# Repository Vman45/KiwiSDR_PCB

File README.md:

[updated 28 May 2018]

Click image for full size.

[© bluebison.net](http://bluebison.net)

KiwiSDR
=======

Software-defined Radio (SDR) and GPS for the BeagleBone Black
----------------------------------------------------------------------

An add-on board ("cape") that turns your Beagle into a web-accessible shortwave receiver.

This repository contains the KiCAD files (schematics, board layout), Gerbers, BOM and other files used to produce the KiwiSDR PCB.
Also included here is the design for an active antenna and bias tee.

**Note: the active antenna and bias tee schematics and PCBs here are still undergoing development and do not work properly. Do not fabricate the PCBs and expect them to work.**

The KiwiSDR software is located in the repository [Beagle_SDR_GPS](https://github.com/jks-prv/Beagle_SDR_GPS/).

### Kickstarter
KiwiSDR had a successful [Kickstarter](https://www.kickstarter.com/projects/1575992013/kiwisdr-beaglebone-software-defined-radio-sdr-with/).

### Details

* Listen live: [SDR.hu](https://sdr.hu/?top=kiwi), [kiwisdr.com](http://kiwisdr.com/public), [rx.linkfanel.net](http://rx.linkfanel.net)
* [Project webpage](http://www.kiwisdr.com/)
* [Operating information: installation, operation, FAQ](http://www.kiwisdr.com/quickstart/)
* Latest [source code commits](https://github.com/jks-prv/Beagle_SDR_GPS/commits/master)
* [Design review document](https://www.dropbox.com/s/i1bjyp1acghnc16/KiwiSDR.design.review.pdf?dl=1)
* [Schematic](http://www.kiwisdr.com/docs/KiwiSDR/kiwi.schematic.pdf), [Gerbers](http://www.kiwisdr.com/docs/KiwiSDR/kiwi.gerbers.tar), [Active antenna](http://www.kiwisdr.com/docs/KiwiSDR/ant.pdf), [BOM ODS](http://www.kiwisdr.com/docs/KiwiSDR/kiwi.bom.ods), [BOM XLS](http://www.kiwisdr.com/docs/KiwiSDR/kiwi.bom.xls)

### Description
This SDR is a bit different. It has a web interface that can be used by up to four separate listeners. Each one listening and tuning an independent frequency simultaneously. See the screenshots below.

### Components
* SDR covering the 10 kHz to 30 MHz (VLF-HF) spectrum.
* Web interface based on [OpenWebRX](http://openwebrx.org/) from András Retzler, HA7ILM.
* Integrated software-defined GPS receiver from Andrew Holme's [Homemade GPS Receiver](http://www.aholme.co.uk/GPS/Main.htm).
* LTC 14-bit 65 MHz ADC.
* Xilinx Artix-7 A35 FPGA.
* Skyworks SE4150L GPS front-end.

### Features
* 100% Open Source / Open Hardware.
* Browser-based interface allowing multiple simultaneous user web connections (currently 4).
* Each connection tunes an independent receiver channel over the entire spectrum.
* Waterfall tunes independently of audio and includes zooming and panning.
* Multi-channel, parallel DDC design using bit-width optimized CIC filters.
* Good performance at VLF/LF since we personally spend time monitoring those frequencies.
* Automatic frequency calibration via received GPS timing.
* Easy hardware and software setup. Browser-based configuration interface.

### Status

Give the live receivers a try at the links above. You'll need a recent version of a modern web browser that supports HTML5. The web interface works, with some problems, on mobile devices. But there is no mobile version of the interface yet.

The files of a KiCAD PCB layout of the cape are available. This PCB has been fabricated in production quantities
and shipped to thousands of customers worldwide.
Please email us any comments you have after reviewing the design document above. The active antenna and injector PCBs have been fabricated and are undergoing development.

### Objectives

We wanted to design an SDR that provides certain features, at a low price point, that we felt weren't covered by current devices. The SDR must be web-accessible and simple to setup and use.
We also wanted to provide a self-contained platform for experimentation with SDR and GPS techniques. 

Most importantly, We'd really like to see a significant number of web-enabled, wide-band SDRs deployed in diverse locations world-wide because that makes possible some really interesting applications and experiments.

### Operation

Users can purchase just the KiwiSDR board or a complete "kit" consisting of the board, BeagleBone Green (software pre-installed), enclosure (assembly required), and GPS antenna (see [here](http://www.kiwisdr.com/)).
The software will try to automatically open up an incoming port through whatever Internet firewall/router may exist on the local network, but the user may have to perform this step manually. An antenna solution must be provided. An adequate power supply to the Beagle (e.g. 5V @ 2A) will also be required.

Four channels of audio and waterfall streamed over the Internet 24/7 requires about 30 GB per month. This is a common cap for many residential broadband plans. An automatic dynamic-DNS system is already part of the software so a web link to the SDR is immediately available with no configuration. Of course the system can be configured to only allow connections from the local network and ignore Internet connection requests.

### Web interface screenshots

Click images for full size.

View of entire 0-30 MHz range:

Moderate zoom of medium-wave broadcast band with spectrum display on top enabled:

Over-the-horizon-radar (OTHR) from Cyprus showing short-term ionospheric fluctuations:

VLF/LF reception in New Zealand

| kHz | Station | Location | Signal |
| :-- | :------ | :------- | :----- |
| 12.88 | Alpha | Khabarovsk & Novosibirsk Russia | Navigation system |
| 17.0 | VTX2 | India | MSK comms |
| 19.8 | NWC | Australia | MSK comms |
| 21.4 | NPM | Hawaii | MSK comms |
| 22.2 | NDT/JJI | Japan | MSK comms |
| 24.1 | (UNID) | Korea, per David L Wilson | FSK comms |
| 40.0 | JJY | Japan | Time signal |
| 45.9 | NSY | Italy | MSK comms |
| 54.0 | NDI | Japan | MSK comms |
| 60.0 | JJY/WWVB | Japan, USA | Time signals |
| 68.5 | BPC | China | Time signal |

Many others heard during different times and conditions.

[end-of-document]

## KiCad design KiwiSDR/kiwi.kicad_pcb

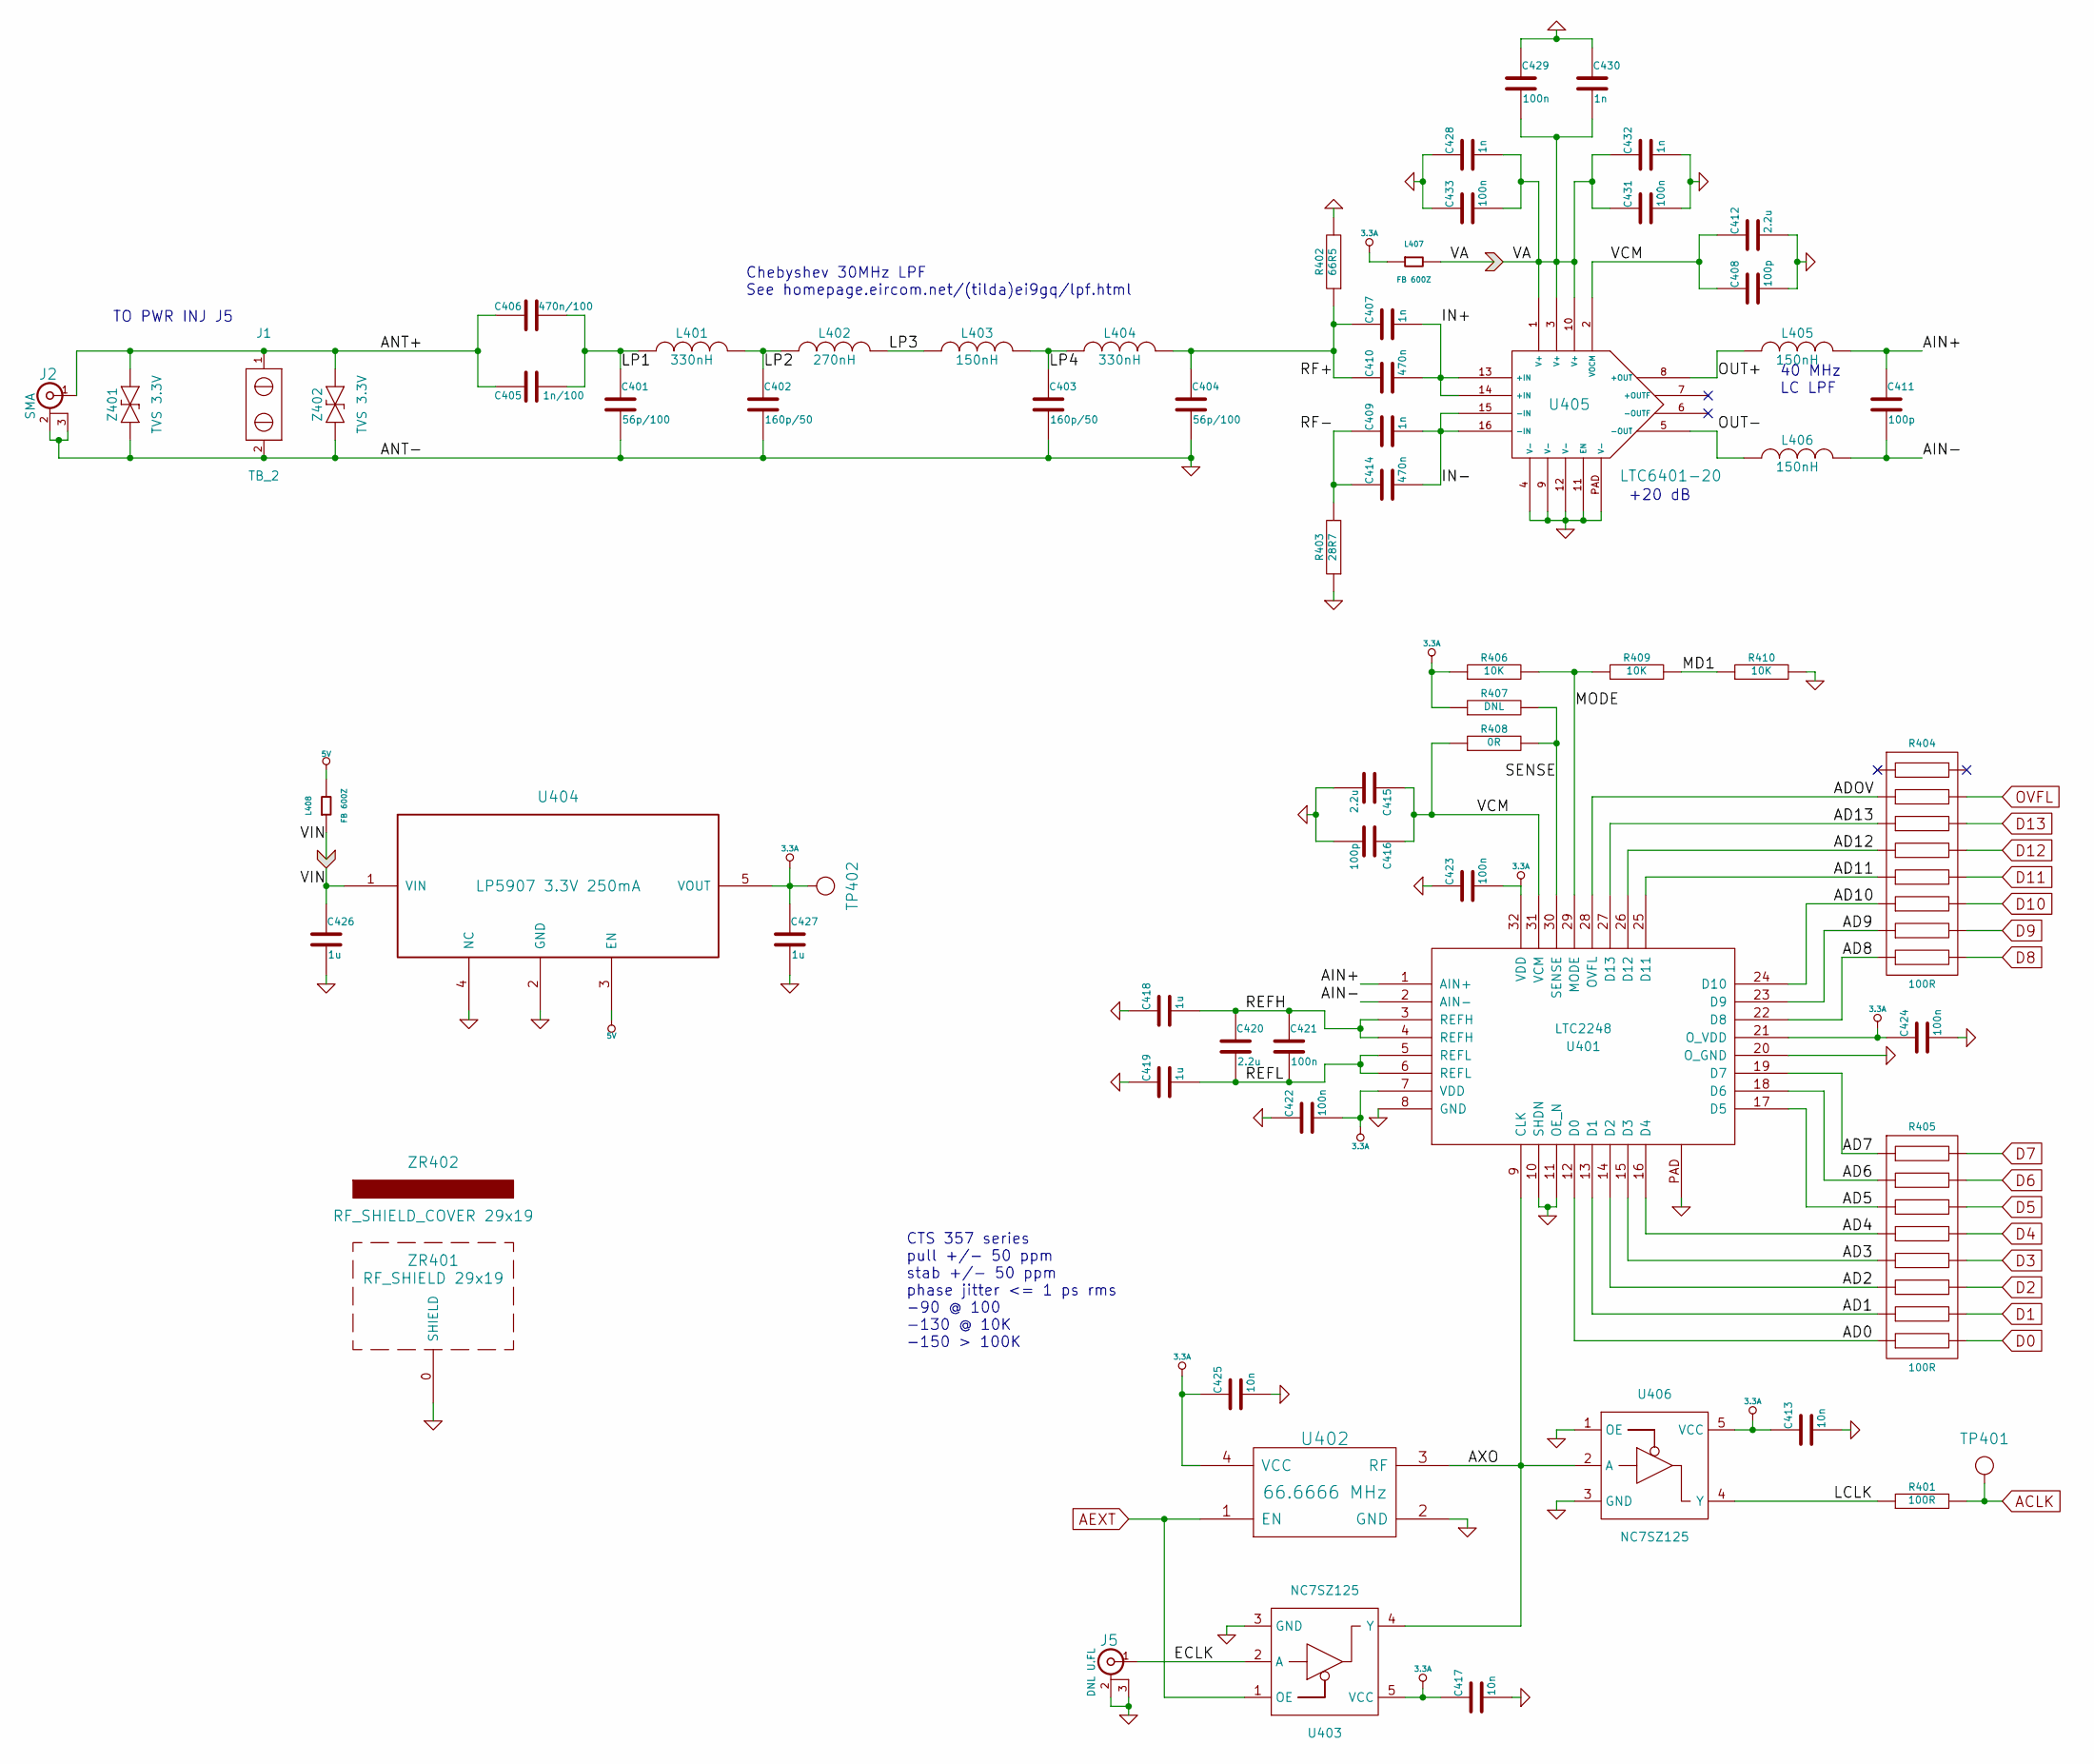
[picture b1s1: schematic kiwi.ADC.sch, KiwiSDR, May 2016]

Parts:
C401, C404: 56p/100; kiwi-SM0402
C402, C403: 160p/50; kiwi-SM0402
C405: 1n/100; kiwi-SM0805
C406: 470n/100; kiwi-SM1206
C407, C409, C428, C430, C432: 1n; kiwi-SM0402
C408, C411, C416: 100p; kiwi-SM0402
C410, C414: 470n; kiwi-SM0402
C412, C415, C420: 2.2u; kiwi-SM0402
C413, C417, C425: 10n; kiwi-SM0402
C418, C419, C426, C427: 1u; kiwi-SM0402
C421, C422, C423, C424, C429, C431, C433: 100n; kiwi-SM0402
J1: TB_2; kiwi-TB_2P_2_54MM
J2: SMA; kiwi-SMA_OPL_EM
J5: DNL U.FL; kiwi-U.FL
L401, L404: 330nH; kiwi-SM0402
L402: 270nH; kiwi-SM0402
L403, L405, L406: 150nH; kiwi-SM0402
L407, L408: FB 600Z; kiwi-SM0402
R401: 100R; kiwi-SM0402
R402: 66R5; kiwi-SM0402
R403: 28R7; kiwi-SM0402
R404, R405: 100R; kiwi-RNET_CAY16_J8
R406, R409, R410: 10K; kiwi-SM0402
R407: DNL; kiwi-SM0402
R408: 0R; kiwi-SM0402
TP401: TEST_POINT; kiwi-TP_600
TP402: TEST_POINT; kiwi-TP_VIA_600
U401: LTC2248; kiwi-QFN32
U402: 66.6666 MHz; kiwi-XO
U403, U406: NC7SZ125; kiwi-SC70_5
U404: LP5907 3.3V 250mA; kiwi-SOT23_5
U405: LTC6401-20; kiwi-QFN16
Z401, Z402: TVS 3.3V; kiwi-SOD323
ZR401: RF_SHIELD 29x19; kiwi-RF_SHIELD_29x19
ZR402: RF_SHIELD_COVER 29x19; kiwi-RF_SHIELD_COVER

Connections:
3.3A: C413.1, C417.1, C422.2, C423.2, C424.1, C425.1, C427.1, L407.1, R406.1, R407.1, TP402.1, U401.7 (VDD), U401.21 (O_VDD), U401.32 (VDD), U402.4 (VCC), U403.5 (VCC), U404.5 (VOUT), U406.5 (VCC)
/ADC/AD0: R405.15, U401.12 (D0)
/ADC/AD1: R405.13, U401.13 (D1)
/ADC/AD2: R405.11, U401.14 (D2)
/ADC/AD3: R405.9, U401.15 (D3)
/ADC/AD4: R405.7, U401.16 (D4)
/ADC/AD5: R405.5, U401.17 (D5)
/ADC/AD6: R405.3, U401.18 (D6)
/ADC/AD7: R405.1, U401.19 (D7)
/ADC/AD8: R404.15, U401.22 (D8)
/ADC/AD9: R404.13, U401.23 (D9)
/ADC/AD10: R404.11, U401.24 (D10)
/ADC/AD11: R404.9, U401.25 (D11)
/ADC/AD12: R404.7, U401.26 (D12)
/ADC/AD13: R404.5, U401.27 (D13)
/ADC/ADOV: R404.3, U401.28 (OVFL)
/ADC/AIN+: C411.1, L405.2, U401.1 (AIN+)
/ADC/AIN-: C411.2, L406.2, U401.2 (AIN-)
/ADC/ANT+: C405.1, C406.1, J1.1, J2.1 (In), Z401.2, Z402.2
/ADC/AXO: U401.9 (CLK), U402.3 (RF), U403.4 (Y), U406.2 (A)
/ADC/ECLK: J5.1 (In), U403.2 (A)
/ADC/IN+: C407.2, C410.2, U405.13 (+IN), U405.14 (+IN)
/ADC/IN-: C409.2, C414.2, U405.15 (-IN), U405.16 (-IN)
/ADC/LCLK: R401.1, U406.4 (Y)
/ADC/LP1: C401.1, C405.2, C406.2, L401.1
/ADC/LP2: C402.1, L401.2, L402.1
/ADC/LP3: L402.2, L403.1
/ADC/LP4: C403.1, L403.2, L404.1
/ADC/MD1: R409.2, R410.1
/ADC/MODE: R406.2, R409.1, U401.29 (MODE)
/ADC/OUT+: L405.1, U405.8 (+OUT)
/ADC/OUT-: L406.1, U405.5 (-OUT)
/ADC/REFH: C418.2, C420.1, C421.1, U401.3 (REFH), U401.4 (REFH)
/ADC/REFL: C419.2, C420.2, C421.2, U401.5 (REFL), U401.6 (REFL)
/ADC/RF+: C404.1, C407.1, C410.1, L404.2, R402.1
/ADC/RF-: C409.1, C414.1, R403.2
/ADC/SENSE: R407.2, R408.2, U401.30 (SENSE)
/ADC/VCM: C408.1, C412.1, C415.1, C416.1, R408.1, U401.31 (VCM), U405.2 (VOCM)
ACLK: R401.2, TP401.1; also elsewhere on the board
AEXT: U402.1 (EN), U403.1 (OE); also elsewhere on the board
D0: R405.16; also elsewhere on the board
D1: R405.14; also elsewhere on the board
D2: R405.12; also elsewhere on the board
D3: R405.10; also elsewhere on the board
D4: R405.8; also elsewhere on the board
D5: R405.6; also elsewhere on the board
D6: R405.4; also elsewhere on the board
D7: R405.2; also elsewhere on the board
D8: R404.16; also elsewhere on the board
D9: R404.14; also elsewhere on the board
D10: R404.12; also elsewhere on the board
D11: R404.10; also elsewhere on the board
D12: R404.8; also elsewhere on the board
D13: R404.6; also elsewhere on the board
OVFL: R404.4; also elsewhere on the board

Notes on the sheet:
CTS 357 series pull +/- 50 ppm stab +/- 50 ppm phase jitter <= 1 ps rms -90 @ 100 -130 @ 10K -150 > 100K
Chebyshev 30MHz LPF See homepage.eircom.net/(tilda)ei9gq/lpf.html
40 MHz LC LPF
+20 dB
TO PWR INJ J5

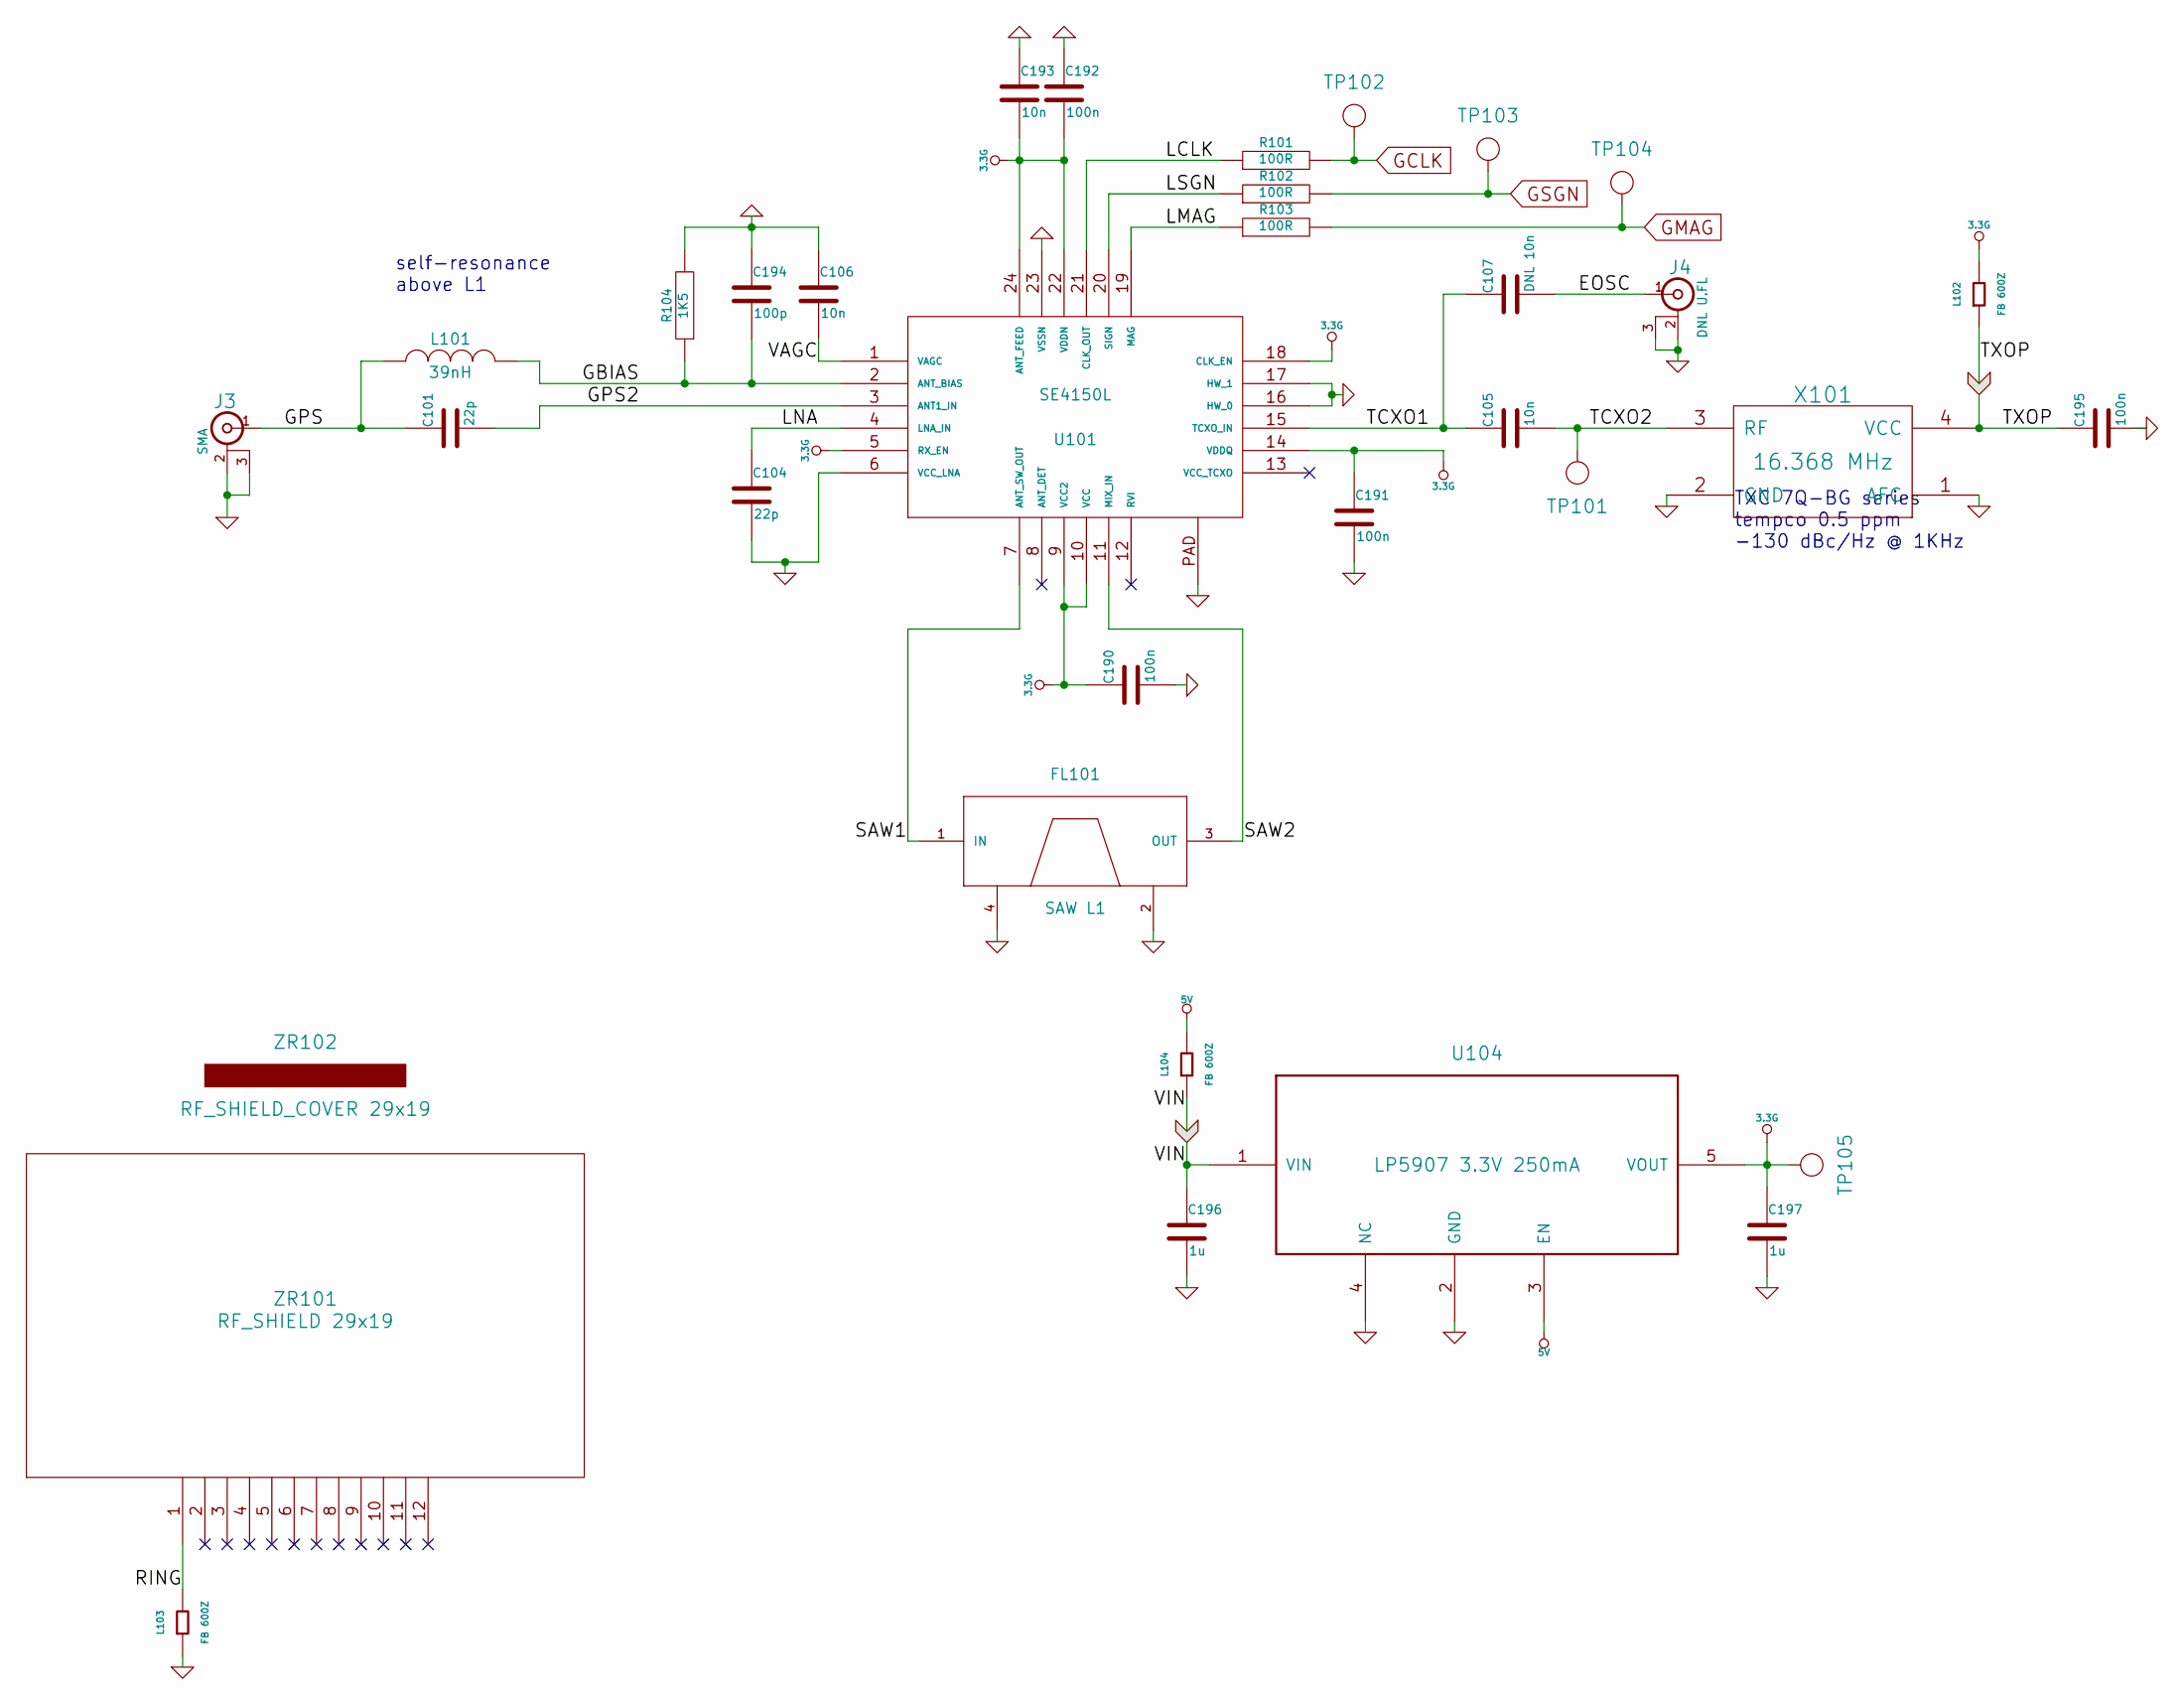
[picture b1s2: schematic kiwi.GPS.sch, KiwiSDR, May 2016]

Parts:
C101, C104: 22p; kiwi-SM0402
C105, C106, C193: 10n; kiwi-SM0402
C107: DNL 10n; kiwi-SM0402
C190, C191, C192, C195: 100n; kiwi-SM0402
C194: 100p; kiwi-SM0402
C196, C197: 1u; kiwi-SM0402
FL101: SAW L1; kiwi-SAW
J3: SMA; kiwi-SMA_OPL_EM
J4: DNL U.FL; kiwi-U.FL
L101: 39nH; kiwi-SM0402
L102, L103, L104: FB 600Z; kiwi-SM0402
R101, R102, R103: 100R; kiwi-SM0402
R104: 1K5; kiwi-SM0402
TP101, TP105: TEST_POINT; kiwi-TP_600
TP102, TP103, TP104: TEST_POINT; kiwi-TP_VIA_1250
U101: SE4150L; kiwi-QFN24
U104: LP5907 3.3V 250mA; kiwi-SOT23_5
X101: 16.368 MHz; kiwi-TCXO
ZR101: RF_SHIELD 29x19; kiwi-RF_SHIELD_29x19_16P
ZR102: RF_SHIELD_COVER 29x19; kiwi-RF_SHIELD_COVER

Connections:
3.3G: C190.1, C191.1, C192.2, C193.2, C197.1, L102.2, TP105.1, U101.5 (RX_EN), U101.9 (VCC2), U101.10 (VCC), U101.14 (VDDQ), U101.18 (CLK_EN), U101.22 (VDDN), U101.24 (ANT_FEED), U104.5 (VOUT)
/GPS/EOSC: C107.2, J4.1 (In)
/GPS/GBIAS: C194.2, L101.2, R104.1, U101.2 (ANT_BIAS)
/GPS/GPS: C101.1, J3.1 (In), L101.1
/GPS/GPS2: C101.2, U101.3 (ANT1_IN)
/GPS/LCLK: R101.1, U101.21 (CLK_OUT)
/GPS/LMAG: R103.1, U101.19 (MAG)
/GPS/LNA: C104.1, U101.4 (LNA_IN)
/GPS/LSGN: R102.1, U101.20 (SIGN)
/GPS/RING: L103.2, ZR101.1
/GPS/SAW1: FL101.1 (IN), U101.7 (ANT_SW_OUT)
/GPS/SAW2: FL101.3 (OUT), U101.11 (MIX_IN)
/GPS/TCXO1: C105.1, C107.1, U101.15 (TCXO_IN)
/GPS/TCXO2: C105.2, TP101.1, X101.3 (RF)
/GPS/VAGC: C106.2, U101.1 (VAGC)
GCLK: R101.2, TP102.1; also elsewhere on the board
GMAG: R103.2, TP104.1; also elsewhere on the board
GSGN: R102.2, TP103.1; also elsewhere on the board

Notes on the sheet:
self-resonance above L1
TXC 7Q-BG series tempco 0.5 ppm -130 dBc/Hz @ 1KHz

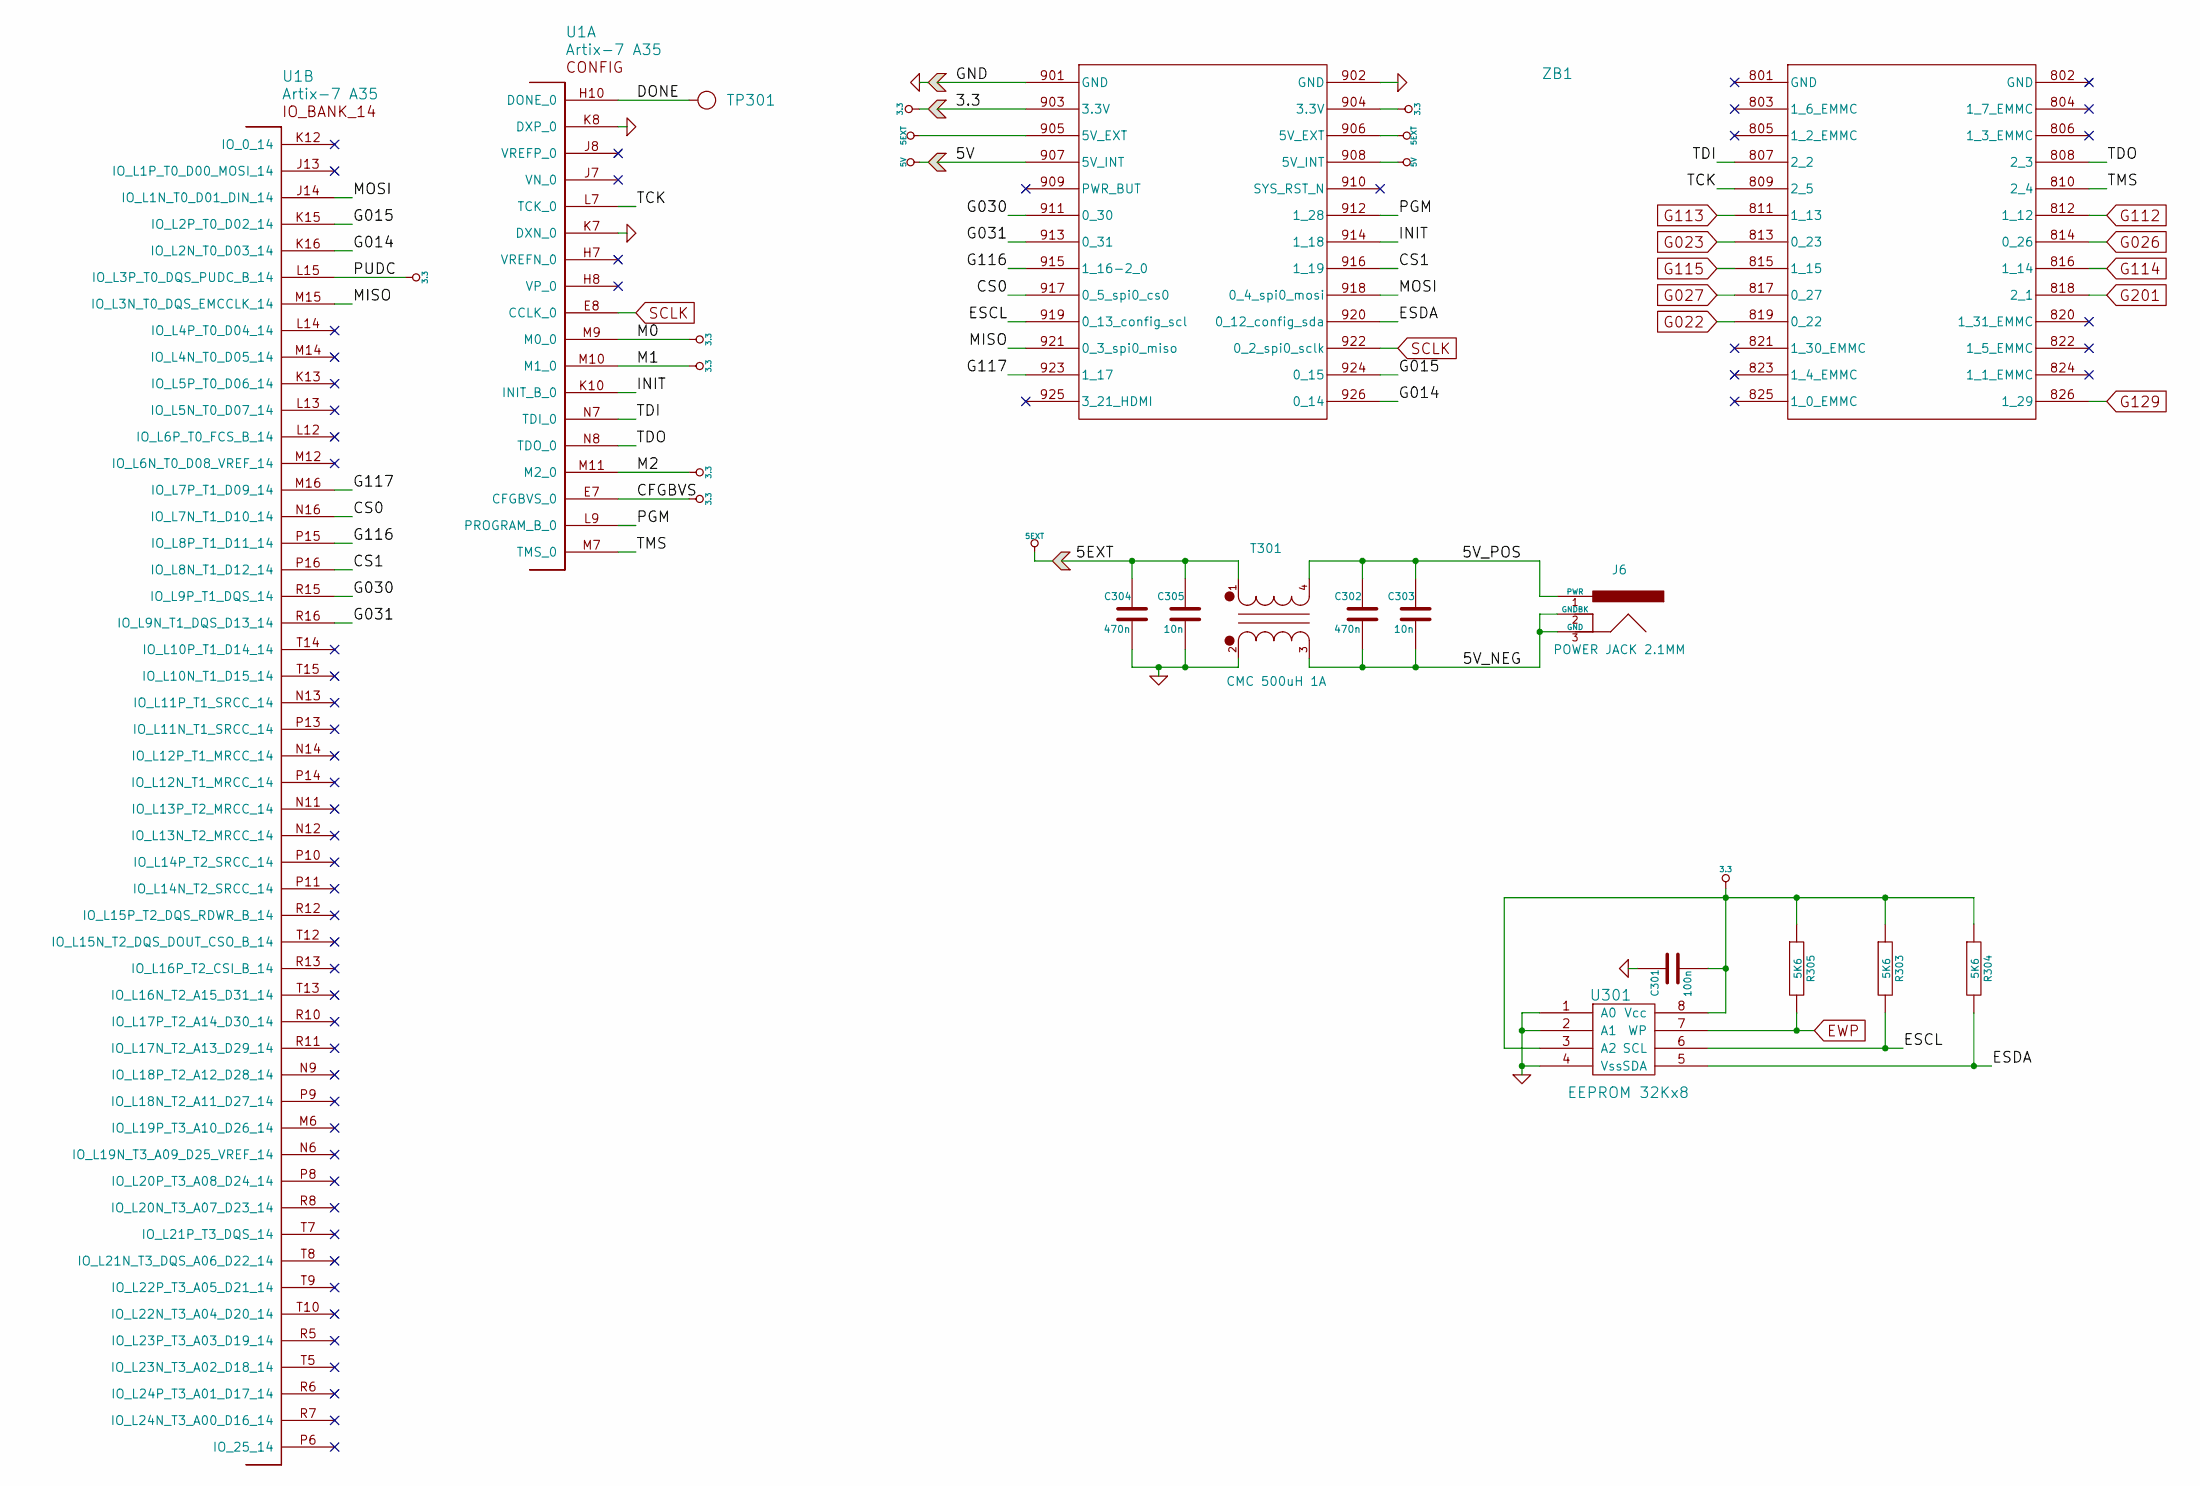
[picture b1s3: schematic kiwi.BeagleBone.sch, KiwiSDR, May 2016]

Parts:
C301: 100n; kiwi-SM0402
C302, C304: 470n; kiwi-SM0402
C303, C305: 10n; kiwi-SM0402
J6: POWER JACK 2.1MM; kiwi-JACK_2_1MM_TH
R303, R304, R305: 5K6; kiwi-SM0402
T301: CMC 500uH 1A; kiwi-CMC
TP301: TEST_POINT; kiwi-TP_VIA_600
U1: Artix-7 A35; kiwi-FTG256
U301: EEPROM 32Kx8; kiwi-TSSOP8
ZB1: HEADER 13x2; kiwi-BEAGLEBONE_BLACK

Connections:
/BeagleBone/5V_NEG: C302.2, C303.2, J6.2 (GNDBK), J6.3 (GND), T301.3
/BeagleBone/5V_POS: C302.1, C303.1, J6.1 (PWR), T301.4
/BeagleBone/CS0: U1.N16 (IO_L7N_T1_D10_14), ZB1.917 (0_5_spi0_cs0)
/BeagleBone/CS1: U1.P16 (IO_L8N_T1_D12_14), ZB1.916 (1_19)
/BeagleBone/DONE: TP301.1, U1.H10 (DONE_0)
/BeagleBone/ESCL: R303.2, U301.6 (SCL), ZB1.919 (0_13_config_scl)
/BeagleBone/ESDA: R304.2, U301.5 (SDA), ZB1.920 (0_12_config_sda)
/BeagleBone/G014: U1.K16 (IO_L2N_T0_D03_14), ZB1.926 (0_14)
/BeagleBone/G015: U1.K15 (IO_L2P_T0_D02_14), ZB1.924 (0_15)
/BeagleBone/G030: U1.R15 (IO_L9P_T1_DQS_14), ZB1.911 (0_30)
/BeagleBone/G031: U1.R16 (IO_L9N_T1_DQS_D13_14), ZB1.913 (0_31)
/BeagleBone/G116: U1.P15 (IO_L8P_T1_D11_14), ZB1.915 (1_16-2_0)
/BeagleBone/G117: U1.M16 (IO_L7P_T1_D09_14), ZB1.923 (1_17)
/BeagleBone/INIT: U1.K10 (INIT_B_0), ZB1.914 (1_18)
/BeagleBone/MISO: U1.M15 (IO_L3N_T0_DQS_EMCCLK_14), ZB1.921 (0_3_spi0_miso)
/BeagleBone/MOSI: U1.J14 (IO_L1N_T0_D01_DIN_14), ZB1.918 (0_4_spi0_mosi)
/BeagleBone/PGM: U1.L9 (PROGRAM_B_0), ZB1.912 (1_28)
/BeagleBone/TCK: U1.L7 (TCK_0), ZB1.809 (2_5)
/BeagleBone/TDI: U1.N7 (TDI_0), ZB1.807 (2_2)
/BeagleBone/TDO: U1.N8 (TDO_0), ZB1.808 (2_3)
/BeagleBone/TMS: U1.M7 (TMS_0), ZB1.810 (2_4)
EWP: R305.2, U301.7 (WP); also elsewhere on the board
G022: ZB1.819 (0_22); also elsewhere on the board
G023: ZB1.813 (0_23); also elsewhere on the board
G026: ZB1.814 (0_26); also elsewhere on the board
G027: ZB1.817 (0_27); also elsewhere on the board
G112: ZB1.812 (1_12); also elsewhere on the board
G113: ZB1.811 (1_13); also elsewhere on the board
G114: ZB1.816 (1_14); also elsewhere on the board
G115: ZB1.815 (1_15); also elsewhere on the board
G129: ZB1.826 (1_29); also elsewhere on the board
G201: ZB1.818 (2_1); also elsewhere on the board
SCLK: U1.E8 (CCLK_0), ZB1.922 (0_2_spi0_sclk); also elsewhere on the board

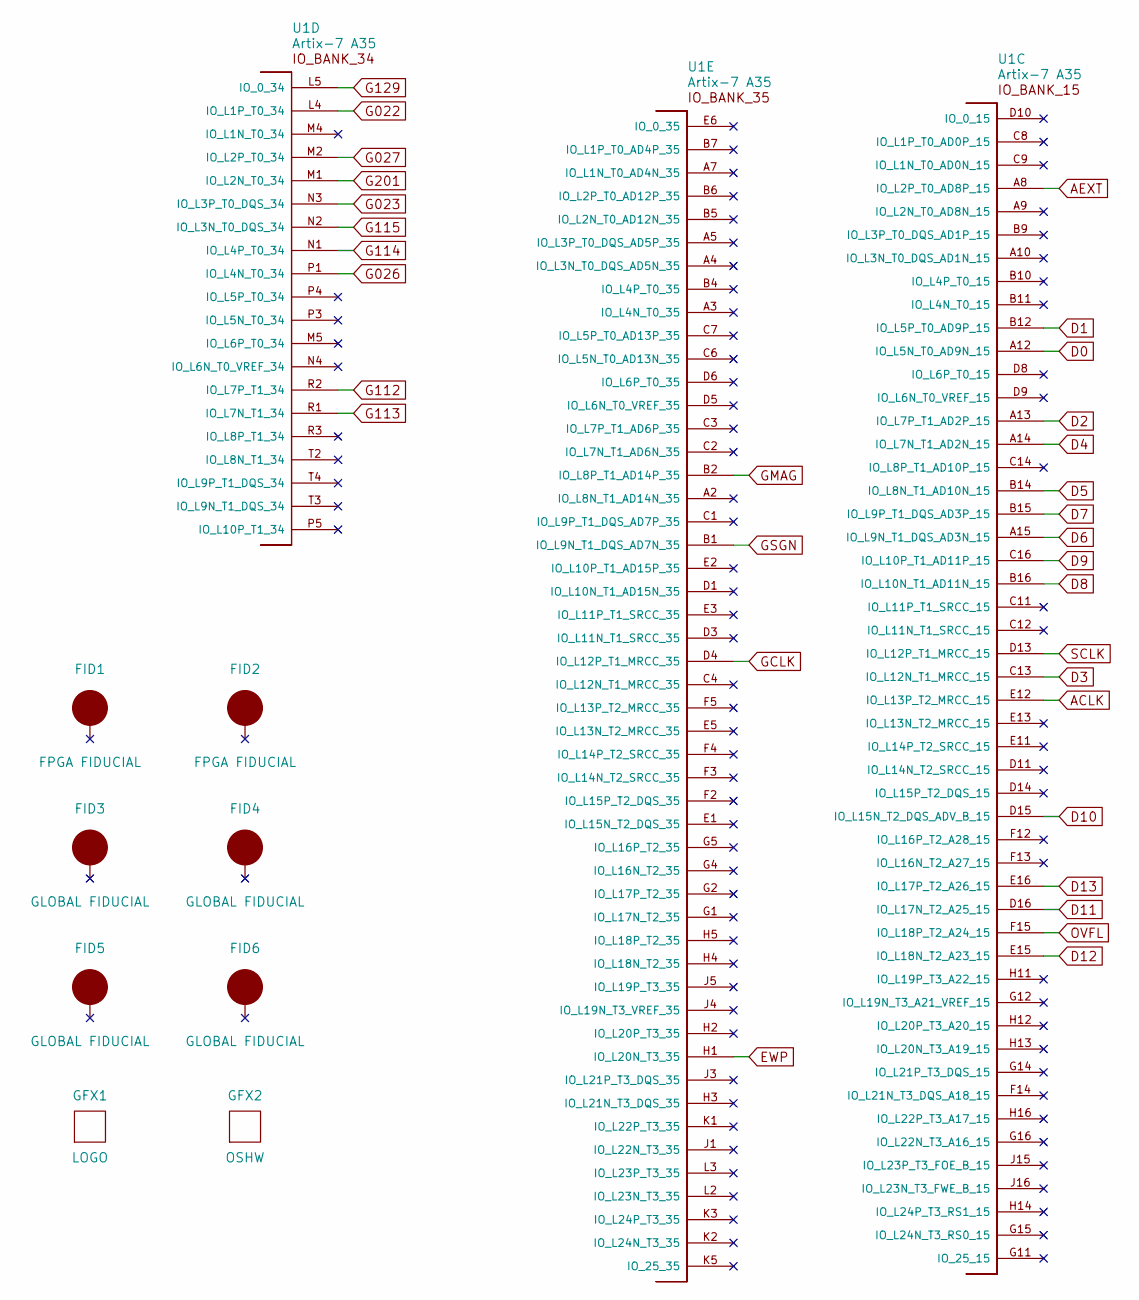
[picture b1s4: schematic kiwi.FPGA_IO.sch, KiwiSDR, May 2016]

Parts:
FID1, FID2: FPGA FIDUCIAL; kiwi-FIDUCIAL
FID3, FID4, FID5, FID6: GLOBAL FIDUCIAL; kiwi-FIDUCIAL
GFX1: LOGO; kiwi-KIWI_10MM
GFX2: OSHW; kiwi-OSHW_6MM
U1: Artix-7 A35; kiwi-FTG256

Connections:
ACLK: U1.E12 (IO_L13P_T2_MRCC_15); also elsewhere on the board
AEXT: U1.A8 (IO_L2P_T0_AD8P_15); also elsewhere on the board
D0: U1.A12 (IO_L5N_T0_AD9N_15); also elsewhere on the board
D1: U1.B12 (IO_L5P_T0_AD9P_15); also elsewhere on the board
D2: U1.A13 (IO_L7P_T1_AD2P_15); also elsewhere on the board
D3: U1.C13 (IO_L12N_T1_MRCC_15); also elsewhere on the board
D4: U1.A14 (IO_L7N_T1_AD2N_15); also elsewhere on the board
D5: U1.B14 (IO_L8N_T1_AD10N_15); also elsewhere on the board
D6: U1.A15 (IO_L9N_T1_DQS_AD3N_15); also elsewhere on the board
D7: U1.B15 (IO_L9P_T1_DQS_AD3P_15); also elsewhere on the board
D8: U1.B16 (IO_L10N_T1_AD11N_15); also elsewhere on the board
D9: U1.C16 (IO_L10P_T1_AD11P_15); also elsewhere on the board
D10: U1.D15 (IO_L15N_T2_DQS_ADV_B_15); also elsewhere on the board
D11: U1.D16 (IO_L17N_T2_A25_15); also elsewhere on the board
D12: U1.E15 (IO_L18N_T2_A23_15); also elsewhere on the board
D13: U1.E16 (IO_L17P_T2_A26_15); also elsewhere on the board
EWP: U1.H1 (IO_L20N_T3_35); also elsewhere on the board
G022: U1.L4 (IO_L1P_T0_34); also elsewhere on the board
G023: U1.N3 (IO_L3P_T0_DQS_34); also elsewhere on the board
G026: U1.P1 (IO_L4N_T0_34); also elsewhere on the board
G027: U1.M2 (IO_L2P_T0_34); also elsewhere on the board
G112: U1.R2 (IO_L7P_T1_34); also elsewhere on the board
G113: U1.R1 (IO_L7N_T1_34); also elsewhere on the board
G114: U1.N1 (IO_L4P_T0_34); also elsewhere on the board
G115: U1.N2 (IO_L3N_T0_DQS_34); also elsewhere on the board
G129: U1.L5 (IO_0_34); also elsewhere on the board
G201: U1.M1 (IO_L2N_T0_34); also elsewhere on the board
GCLK: U1.D4 (IO_L12P_T1_MRCC_35); also elsewhere on the board
GMAG: U1.B2 (IO_L8P_T1_AD14P_35); also elsewhere on the board
GSGN: U1.B1 (IO_L9N_T1_DQS_AD7N_35); also elsewhere on the board
OVFL: U1.F15 (IO_L18P_T2_A24_15); also elsewhere on the board
SCLK: U1.D13 (IO_L12P_T1_MRCC_15); also elsewhere on the board

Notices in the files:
KiwiSDR/kiwi.kicad_pcb:
© John Seamons
